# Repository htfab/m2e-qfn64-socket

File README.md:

# Caravel M.2 to QFN64 socket adapter

Allows testing of unsoldered Caravel chips with the
[official Caravel evaluation board](https://github.com/efabless/caravel_board/tree/main/hardware/development/caravel-dev-v5-M.2)
or other compatible boards such as the [M.2 E-key breakout](https://github.com/htfab/m2e-breakout).

Drop-in replacement for the 
[Caravel M.2 daughtercard](https://github.com/efabless/caravel_board/tree/main/hardware/breakout/caravel-M.2-card-QFN).

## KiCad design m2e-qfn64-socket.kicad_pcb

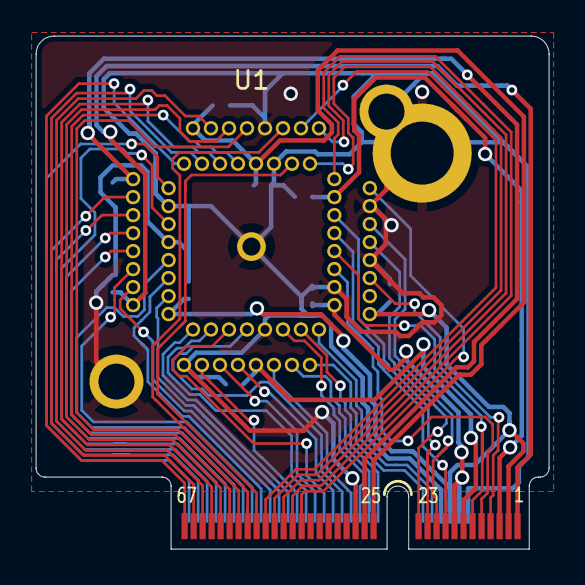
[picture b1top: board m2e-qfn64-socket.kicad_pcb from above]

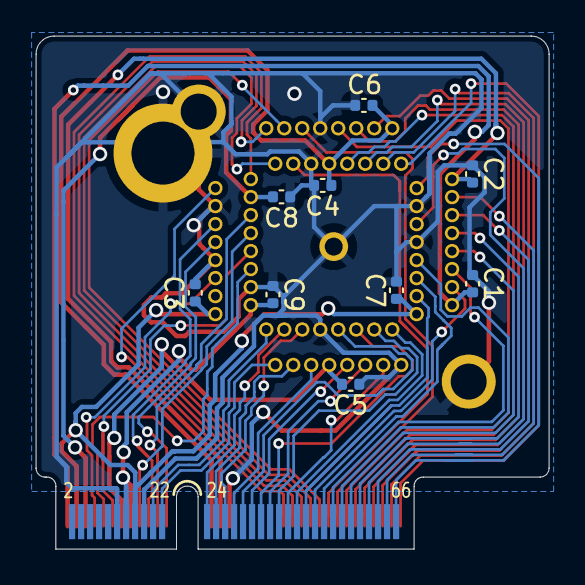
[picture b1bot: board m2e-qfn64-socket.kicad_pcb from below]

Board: 2 copper layers, 28.5 x 28.5 mm, 11 parts (9 on the bottom side), 53 nets.

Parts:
C1, C2, C3, C4, C5, C6, C7, C8, C9: 0.1uf; C_0402_1005Metric
J1: MICROMOD-2222-Generic; m2e-card-large
U1: Caravel; Socket-QFN-64-1EP_9x9mm_P0.5mm

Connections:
Caravel_CSB: J1.11, U1.24 (flash_csb)
Caravel_D0: J1.17, U1.26 (flash_io0)
Caravel_D1: J1.19, U1.27 (flash_io1)
Caravel_SCK: J1.23, U1.25 (flash_clk)
GND: C1.1, C2.1, C3.1, C4.2, C5.1, C6.2, C7.1, C8.2, C9.1, J1.12, J1.18, J1.37 (P29), J1.GND, U1.1 (vssa2), U1.10 (vssd2), U1.20 (vssa), U1.23 (vssd), U1.29 (vssio), U1.38 (vssa1), U1.39 (vssd1), U1.52 (vssa1), U1.56 (vssio), U1.65 (ThermalPad), U1.GND
gpio: J1.21, U1.28 (gpio)
mprj_io[0]: J1.49 (P41), U1.31 (mprj_io[0]_JTAG)
mprj_io[1]_SDO: J1.51 (P43), U1.32 (mprj_io[1]_SDO)
mprj_io[2]_SDI: J1.53 (P45), U1.33 (mprj_io[2]_SDI)
mprj_io[3]_CSB: J1.55 (P47), U1.34 (mprj_io[3]_CSB)
mprj_io[4]_SCK: J1.57 (P49), U1.35 (mprj_io[4]_SCK)
mprj_io[5]_ser_rx: J1.59 (P51), U1.36 (mprj_io[5]_ser_rx)
mprj_io[6]_ser_tx: J1.61 (P53), U1.37 (mprj_io[6]_ser_tx)
mprj_io[7]: J1.63 (P55), U1.41 (mprj_io[7])
mprj_io[8]: J1.65 (P57), U1.42 (mprj_io[8])
mprj_io[9]: J1.67 (P59), U1.43 (mprj_io[9])
mprj_io[10]: J1.69 (P61), U1.44 (mprj_io[10])
mprj_io[11]: J1.71 (P63), U1.45 (mprj_io[11])
mprj_io[12]: J1.73 (P65), U1.46 (mprj_io[12])
mprj_io[13]: J1.75 (P67), U1.48 (mprj_io[13])
mprj_io[14]: J1.74 (P66), U1.50 (mprj_io[14])
mprj_io[15]: J1.72 (P64), U1.51 (mprj_io[15])
mprj_io[16]: J1.70 (P62), U1.53 (mprj_io[16])
mprj_io[17]: J1.68 (P60), U1.54 (mprj_io[17])
mprj_io[18]: J1.66 (P58), U1.55 (mprj_io[18])
mprj_io[19]: J1.64 (P56), U1.57 (mprj_io[19])
mprj_io[20]: J1.62 (P54), U1.58 (mprj_io[20])
mprj_io[21]: J1.60 (P52), U1.59 (mprj_io[21])
mprj_io[22]: J1.58 (P50), U1.60 (mprj_io[22])
mprj_io[23]: J1.56 (P48), U1.61 (mprj_io[23])
mprj_io[24]: J1.54 (P46), U1.62 (mprj_io[24])
mprj_io[25]: J1.52 (P44), U1.2 (mprj_io[25])
mprj_io[26]: J1.50 (P42), U1.3 (mprj_io[26])
mprj_io[27]: J1.48 (P40), U1.4 (mprj_io[27])
mprj_io[28]: J1.46 (P38), U1.5 (mprj_io[28])
mprj_io[29]: J1.44 (P36), U1.6 (mprj_io[29])
mprj_io[30]: J1.42 (P34), U1.7 (mprj_io[30])
mprj_io[31]: J1.40 (P32), U1.8 (mprj_io[31])
mprj_io[32]: J1.38 (P30), U1.11 (mprj_io[32])
mprj_io[33]: J1.36 (P28), U1.12 (mprj_io[33])
mprj_io[34]: J1.34 (P26), U1.13 (mprj_io[34])
mprj_io[35]: J1.32 (P24), U1.14 (mprj_io[35])
mprj_io[36]: J1.22, U1.15 (mprj_io[36])
mprj_io[37]: J1.20, U1.16 (mprj_io[37])
vccd: C9.2, J1.14, J1.15, U1.18 (vccd)
vccd1: C2.2, J1.35 (P27), U1.49 (vccd1)
vccd2: C1.2, J1.1, U1.63 (vccd2)
vdda: C8.1, J1.5, U1.30 (vdda)
vdda1: C4.1, C6.1, J1.33 (P25), U1.40 (vdda1), U1.47 (vdda1)
vdda2: C5.2, J1.13, U1.9 (vdda2)
vddio: C3.2, C7.2, J1.3, J1.16, U1.17 (vddio), U1.64 (vddio)
xclk: J1.9, U1.22 (clock)
~RST: J1.7, U1.21 (resetb)

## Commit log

2024-04-10 add project to version control
